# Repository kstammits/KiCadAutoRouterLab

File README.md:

# Karltron Autorouter

> **Status:** Early stage — works on real boards (tube111, DCCF), DRC-validated. Expect rough edges. Use at your own risk.
> Part of the KiCad AutoRouter Lab project.

Pure-Python autorouter for KiCad: drop a `.kicad_pcb` into the web UI or run headless, get routed tracks back. No `pcbnew` scripting, no C++ plugins.

**Workflow: 1 Load → 2 Place (Step / Run + Accept) → 3 Route → 4 DRC + Download.**

| What it does | How you reach it |
|--------------|------------------|
| **Per-pad force placement** — connected pads attract, all pads repel; parts rotate and slide around locked anchors | Place tab → Step / Run / Accept; Regime presets (Scatter start, Placed-board polish, Tidy align); ghosts as keepout walls / attractors |
| **Grid A* routing** — clearance-aware, per-net widths, power-rail overrides, GND pours passable-at-toll with auto-stitching | Route tab → Route (selection, else all unprotected) / Polish (always effort 3) / Select Unrouted / Refine Order; 2-layer / 4-layer mode switch |
| **Power integrity (report only)** — inlet-anchored DC-resistance screening, mated-pair bridges | Route tab → Power integrity + Mated pairs sections |
| **DRC gate** — `kicad-cli pcb drc` runs on writeback; nothing DRC-dirty is stamped silently | Top bar → Run DRC, then Download |
| **Review & share** — motion playback, force vectors, context save/load, copy-link presets | Motion bar, Show proposal / forces toggles, Save/Load ctx, Copy link |

---

## Quick Start (2 minutes)

```bash
git clone https://github.com/kstammits/KiCadAutoRouterLab.git
cd KiCadAutoRouterLab
python -m venv .venv
.venv/bin/pip install -e ".[dev]" --constraint requirements-lock.txt
.venv/bin/python ui/server.py
# Opens http://127.0.0.1:8000
```

1. **Load** — drag `tests/fixtures/tube111.kicad_pcb` onto the page.
2. **Place** — select parts, **Step** (5 iters) or **Run** (to convergence), **Accept**. Alt+click pins a part.
3. **Route** — Route tab → select nets → **Route** (empty selection routes all unprotected); **Polish** re-smooths at full effort without re-searching.
4. **DRC** — tick **DRC**, **Run DRC**, then **Download** the board.

Headless: `scripts/run_autoroute.py board.kicad_pcb -o out.kicad_pcb --step-iterations 5 --max-total-iterations 500`. Same core; the UI adds SVG view, motion playback, sliders.

Test boards: `tests/fixtures/tube111.kicad_pcb` (105 parts, 73 nets) and `tests/fixtures/DCCF.sved.kicad_pcb` (audio, split rails).

---

## Routing Controls

| Control | Typical Range |
|---------|---------------|
| **Track / Power Width** | 0.15–0.25 / 0.4–0.8 mm; per-net override, then netclass, then power flag |
| **Via Cost / Clearance** | 3–10 mm per via; 0.15–0.25 mm spacing |
| **Grid Resolution** | 0.1 mm default (0.15–0.2 for scouting; finer than 0.1 rarely pays) |
| **Smoothing Effort** | 0 = raw search path … 2 = full arcs (default), 3 = high-effort retry (route-time smoothing + auto-polish); the **Polish** button always runs at 3 on its scope (selection, else routed copper) and falls back to a scoped re-route when the board changed since routing |
| **GND Stitching / Strip GND Blockers** | On (2-layer mode) — stitching repairs pour islands; strip evicts only GND copper, never signals |
| **2-layer / 4-layer** | 2-layer collapses to genuine 2-layer on export; 4-layer taps inner planes with stub+vias (`fanout_vias_added`) |

Details live in the manual and glossary (links below), not here.

---

## Keyboard Shortcuts

`A` select unlocked · `Shift+click` multi-select · `Alt+click` pin · wheel zoom · drag pan · `Fit` reset · `Escape` clear.

---

## Performance

Indicative desktop wall-clock (±30%), measured locally — regenerate with `scripts/benchmark_*.py` (`docs/benchmarks/` is untracked; see its README).

| Task | Typical time |
|------|--------------|
| Placement **Step** (5 iters, ~100 parts) | < 1 s |
| Placement **Run** to budget (1000 iters) | ~25–35 s |
| tube111 full signal set (60 nets, 0.1 mm) | ~15 s, 60/60 routed |
| DCCF full signal set (44 nets) | ~45 s |
| GND stitch + pour repair | ~1–3 s |

Rules of thumb: placement costs ~N^1.2–1.5 per iteration — estimate per-iteration cost × iterations. Routing is ~1 s/net on healthy boards.

---

## Learn More

| Doc | What You'll Find |
|-----|------------------|
| [`ui/manual.html`](ui/manual.html) | **User:** Placement manual with live before/after examples (placement only; routing lives in the app Route tab) |
| [`docs/autorouting_glossary.md`](docs/autorouting_glossary.md) | **User:** Pipeline stages, terminology, algorithm guidance |
| [`docs/si_force_laws.md`](docs/si_force_laws.md) | **Dev reference:** Placement force laws and parameter defaults |
| [`docs/physics_primer.qmd`](docs/physics_primer.qmd) | **Dev reference:** Force-law primer with figures and math |
| [`docs/roadmap.md`](docs/roadmap.md) | **Dev:** Open work |
| [`docs/README.md`](docs/README.md) | **Dev:** Upstream references with fetch recipes |

Regenerate the manual/figures with `.venv/bin/python scripts/gen_manual.py`, or everything (figures + manual + primer) with `./scripts/regen_docs.sh [--only-manual | --skip-quarto | --pdf]`.

---

## Requirements

- Python 3.11+, `.venv` with project deps (`pip install -e ".[dev]" --constraint requirements-lock.txt`, ~600 MB with dev extras)
- KiCad 10.x `kicad-cli` for DRC validation (recommended; `pcbnew` module not needed)

---

## License

GPL-3.0-or-later. See [`LICENSE`](LICENSE).

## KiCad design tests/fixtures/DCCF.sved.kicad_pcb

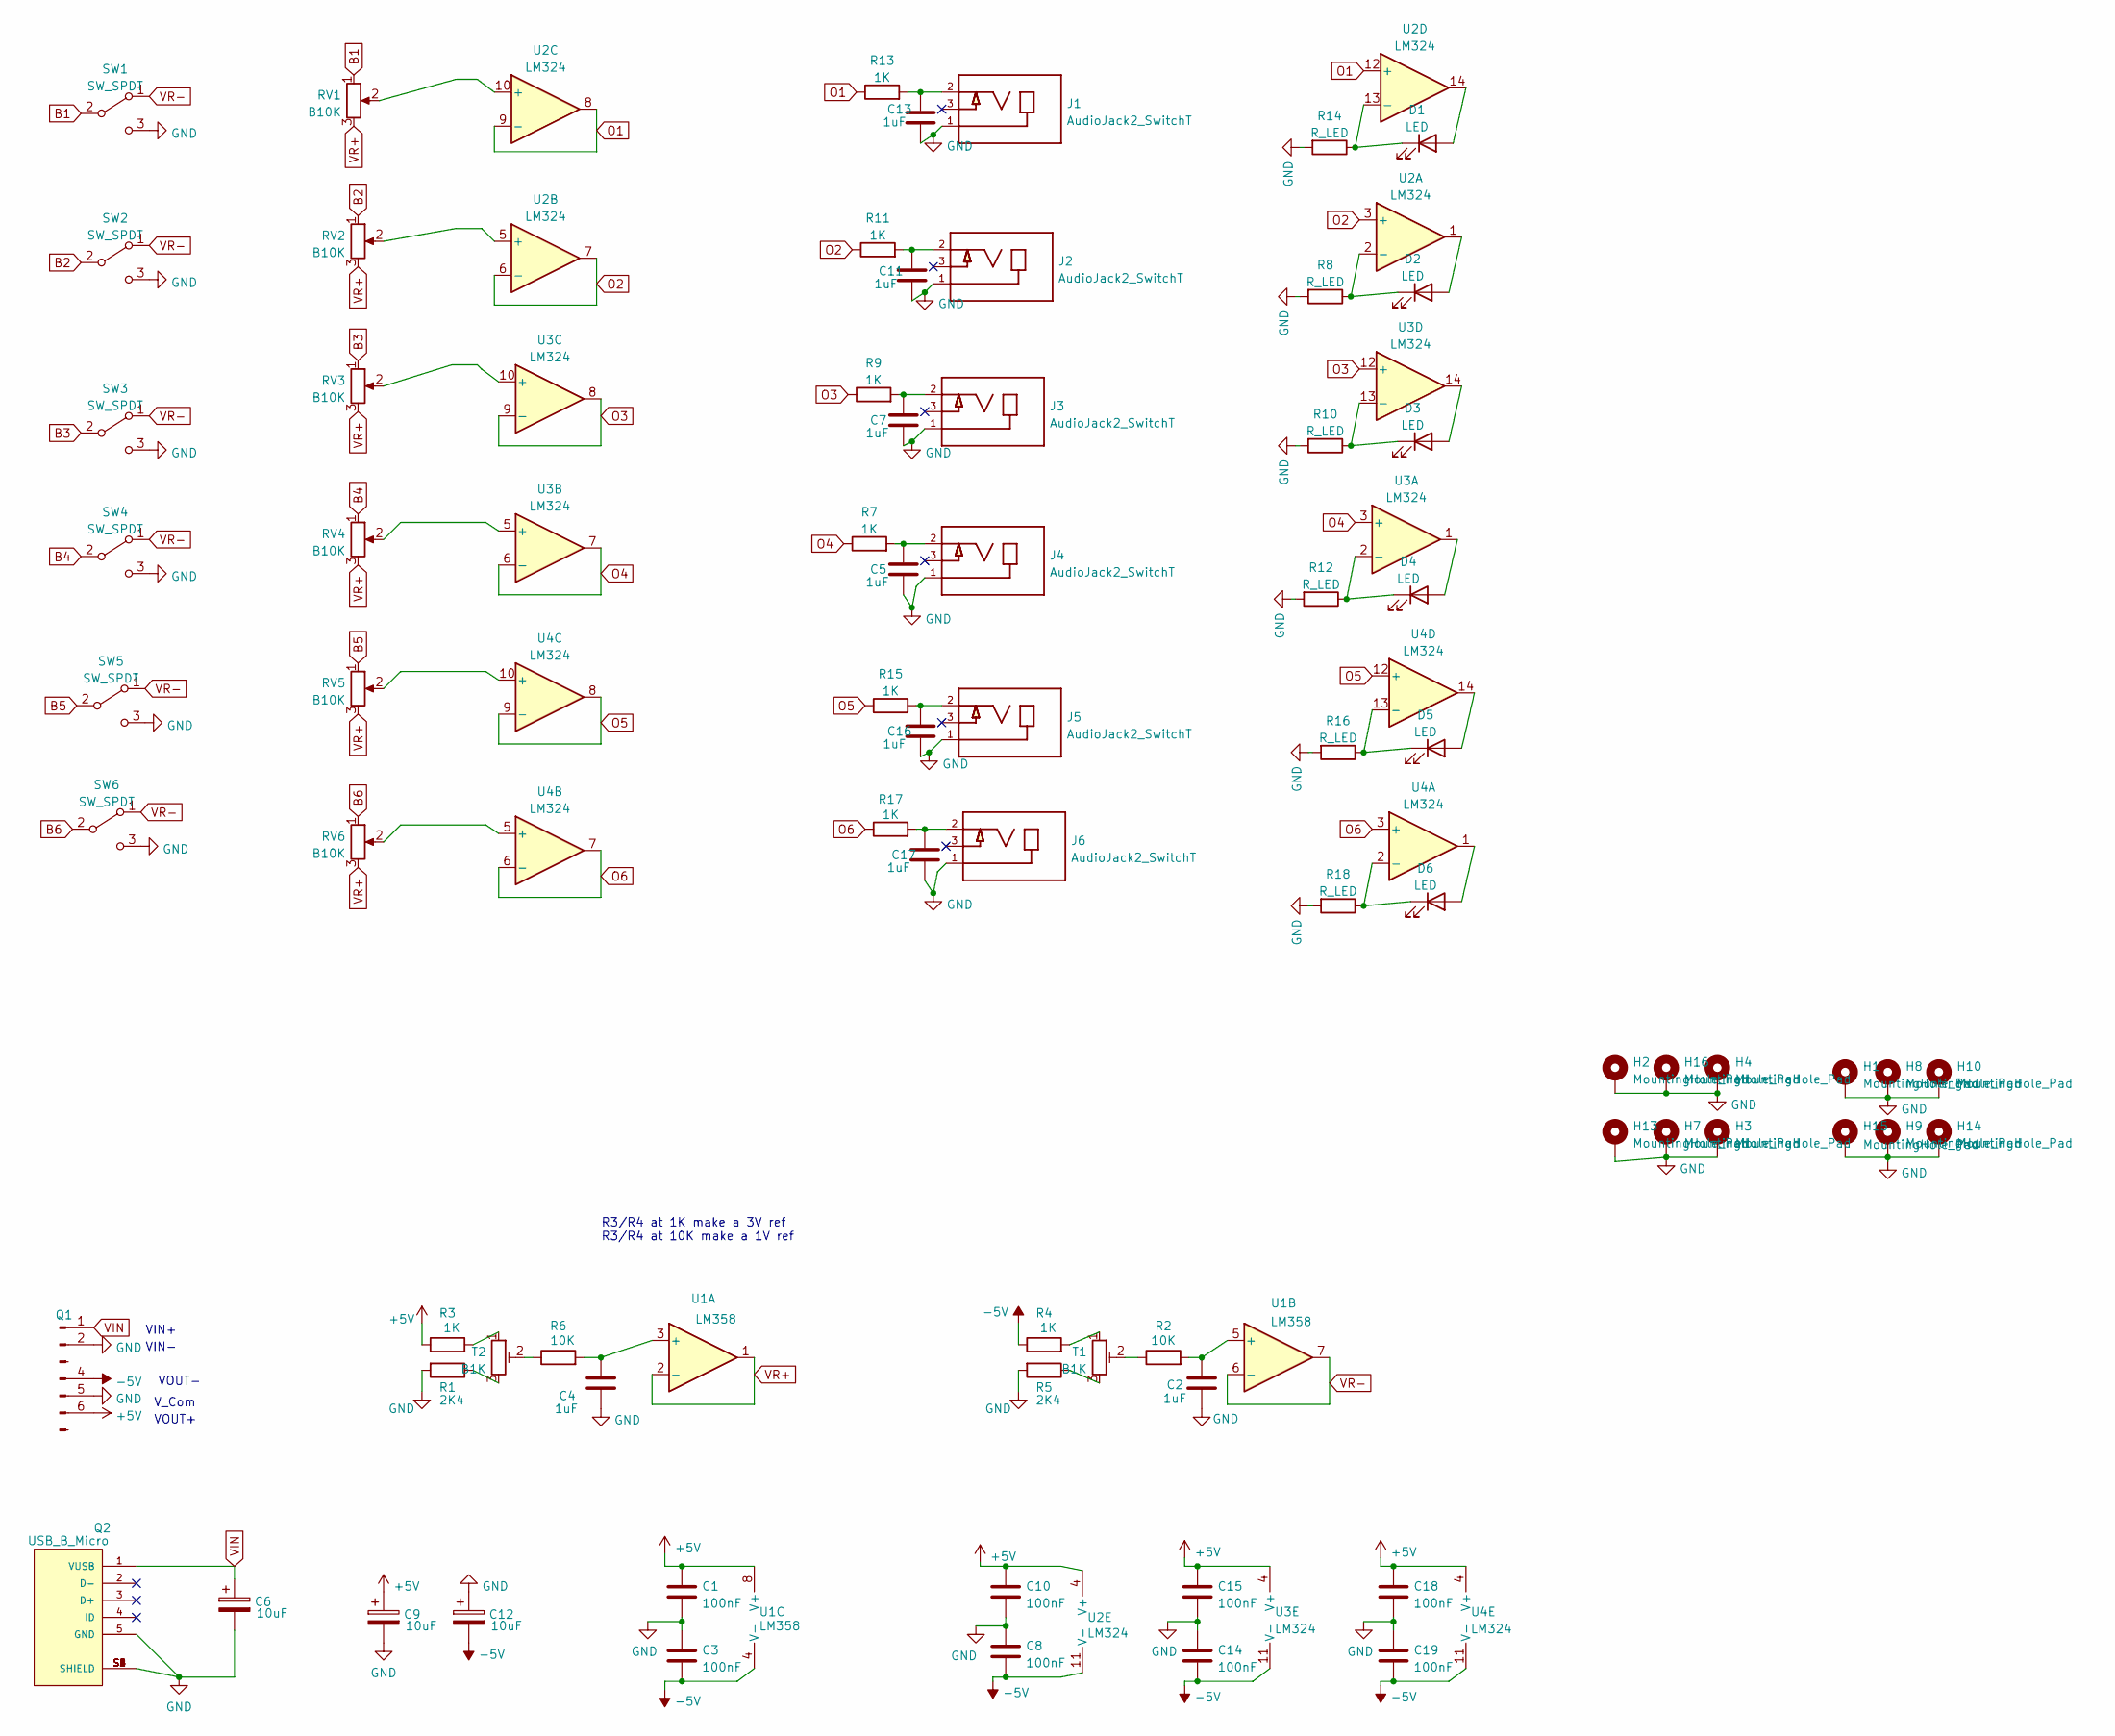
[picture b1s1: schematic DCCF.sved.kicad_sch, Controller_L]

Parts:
C1, C3, C8, C10, C14, C15, C18, C19: 100nF; C_Disc_D5.0mm_W2.5mm_P5.00mm
C2, C4, C5, C7, C11, C13, C16, C17: 1uF; C_Disc_D5.0mm_W2.5mm_P5.00mm
C6, C9, C12: 10uF; CP_Radial_D6.3mm_P2.50mm
D1, D2, D3, D4, D5, D6: LED; LED_D5.0mm
H1, H2, H3, H4, H7, H8, H9, H10, H13, H14, H15, H16: MountingHole_Pad; MountingHole_3.2mm_M3_Pad
J1, J2, J3, J4, J5, J6: AudioJack2_SwitchT; CUI_MJ-3536N; PART_REV B
Q1: Conn_01x07_Male; PinHeader_1x07_P2.54mm_Vertical
Q2: USB_B_Micro; FCI_10118193-0001LF
R1, R5: 2K4; R_Axial_DIN0207_L6.3mm_D2.5mm_P10.16mm_Horizontal
R2, R6: 10K; R_Axial_DIN0207_L6.3mm_D2.5mm_P10.16mm_Horizontal
R3, R4, R7, R9, R11, R13, R15, R17: 1K; R_Axial_DIN0207_L6.3mm_D2.5mm_P10.16mm_Horizontal
R8, R10, R12, R14, R16, R18: R_LED; R_Axial_DIN0207_L6.3mm_D2.5mm_P10.16mm_Horizontal
RV1, RV2: B10K; Potentiometer_Alpha_RD901F-40-00D_Single_Vertical
RV3, RV4, RV5, RV6: B10K; Potentiometer_Bourns_PTA6043_Single_Slide
SW1, SW2, SW3, SW4, SW5, SW6: SW_SPDT; SPDT_Tayda-A5111
T1, T2: B1K; Potentiometer_Bourns_3296W_Vertical
U1: LM358; DIP-8_W7.62mm_Socket
U2, U3, U4: LM324; DIP-14_W7.62mm_Socket

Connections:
+5V: C1.1, C9.1, C10.1, C15.1, C18.1, Q1.6, R3.1, U1.8 (V+), U2.4 (V+), U3.4 (V+), U4.4 (V+)
-5V: C3.2, C8.2, C12.2, C14.2, C19.2, Q1.4, R4.1, U1.4 (V-), U2.11 (V-), U3.11 (V-), U4.11 (V-)
B1: RV1.1, SW1.2 (B)
B2: RV2.1, SW2.2 (B)
B3: RV3.1, SW3.2 (B)
B4: RV4.1, SW4.2 (B)
B5: RV5.1, SW5.2 (B)
B6: RV6.1, SW6.2 (B)
GND: C1.2, C2.2, C3.1, C4.2, C5.2, C6.2, C7.2, C8.1, C9.2, C10.2, C11.2, C12.1, C13.2, C14.1, C15.2, C16.2, C17.2, C18.2, C19.1, H1.1, H2.1, H3.1, H4.1, H7.1, H8.1, H9.1, H10.1, H13.1, H14.1, H15.1, H16.1, J1.1, J2.1, J3.1, J4.1, J5.1, J6.1, Q1.2, Q1.5, Q2.5 (GND), Q2.S1 (SHIELD), Q2.S2 (SHIELD), Q2.S3 (SHIELD), Q2.S4 (SHIELD), Q2.S5 (SHIELD), Q2.S6 (SHIELD), R1.2, R5.2, R8.2, R10.2, R12.2, R14.2, R16.2, R18.2, SW1.3 (C), SW2.3 (C), SW3.3 (C), SW4.3 (C), SW5.3 (C), SW6.3 (C); also elsewhere on the board
unnamed: C2.1, R2.2, U1.5 (+)
unnamed: C4.1, R6.2, U1.3 (+)
unnamed: C5.1, J4.2, R7.2
unnamed: C7.1, J3.2, R9.2
unnamed: C11.1, J2.2, R11.2
unnamed: C13.1, J1.2, R13.2
unnamed: C16.1, J5.2, R15.2
unnamed: C17.1, J6.2, R17.2
unnamed: D1.1 (K), R14.1, U2.13 (-)
unnamed: D1.2 (A), U2.14
unnamed: D2.1 (K), R8.1, U2.2 (-)
unnamed: D2.2 (A), U2.1
unnamed: D3.1 (K), R10.1, U3.13 (-)
unnamed: D3.2 (A), U3.14
unnamed: D4.1 (K), R12.1, U3.2 (-)
unnamed: D4.2 (A), U3.1
unnamed: D5.1 (K), R16.1, U4.13 (-)
unnamed: D5.2 (A), U4.14
unnamed: D6.1 (K), R18.1, U4.2 (-)
unnamed: D6.2 (A), U4.1
unnamed: R1.1, T2.3
unnamed: R2.1, T1.2
unnamed: R3.2, T2.1
unnamed: R4.2, T1.1
unnamed: R5.1, T1.3
unnamed: R6.1, T2.2
unnamed: RV1.2, U2.10 (+)
unnamed: RV2.2, U2.5 (+)
unnamed: RV3.2, U3.10 (+)
unnamed: RV4.2, U3.5 (+)
unnamed: RV5.2, U4.10 (+)
unnamed: RV6.2, U4.5 (+)
O1: R13.1, U2.8, U2.9 (-), U2.12 (+)
O2: R11.1, U2.3 (+), U2.6 (-), U2.7
O3: R9.1, U3.8, U3.9 (-), U3.12 (+)
O4: R7.1, U3.3 (+), U3.6 (-), U3.7
O5: R15.1, U4.8, U4.9 (-), U4.12 (+)
O6: R17.1, U4.3 (+), U4.6 (-), U4.7
VIN: C6.1, Q1.1, Q2.1 (VUSB)
VR+: RV1.3, RV2.3, RV3.3, RV4.3, RV5.3, RV6.3, U1.1, U1.2 (-)
VR-: SW1.1 (A), SW2.1 (A), SW3.1 (A), SW4.1 (A), SW5.1 (A), SW6.1 (A), U1.6 (-), U1.7

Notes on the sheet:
VIN-
R3/R4 at 1K make a 3V ref R3/R4 at 10K make a 1V ref
VOUT+
V_Com
VOUT-
VIN+

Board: 2 copper layers, 87 parts (0 on the bottom side), 50 nets, no tracks yet.

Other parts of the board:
H5, H6, H6#2, H6#3, H6#4, H6#5: MountingHole_Pad; MountingHole_3.2mm_M3_Pad

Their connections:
GND: H5.1, H6.1, H6#2.1, H6#3.1, H6#4.1, H6#5.1; also elsewhere on the board

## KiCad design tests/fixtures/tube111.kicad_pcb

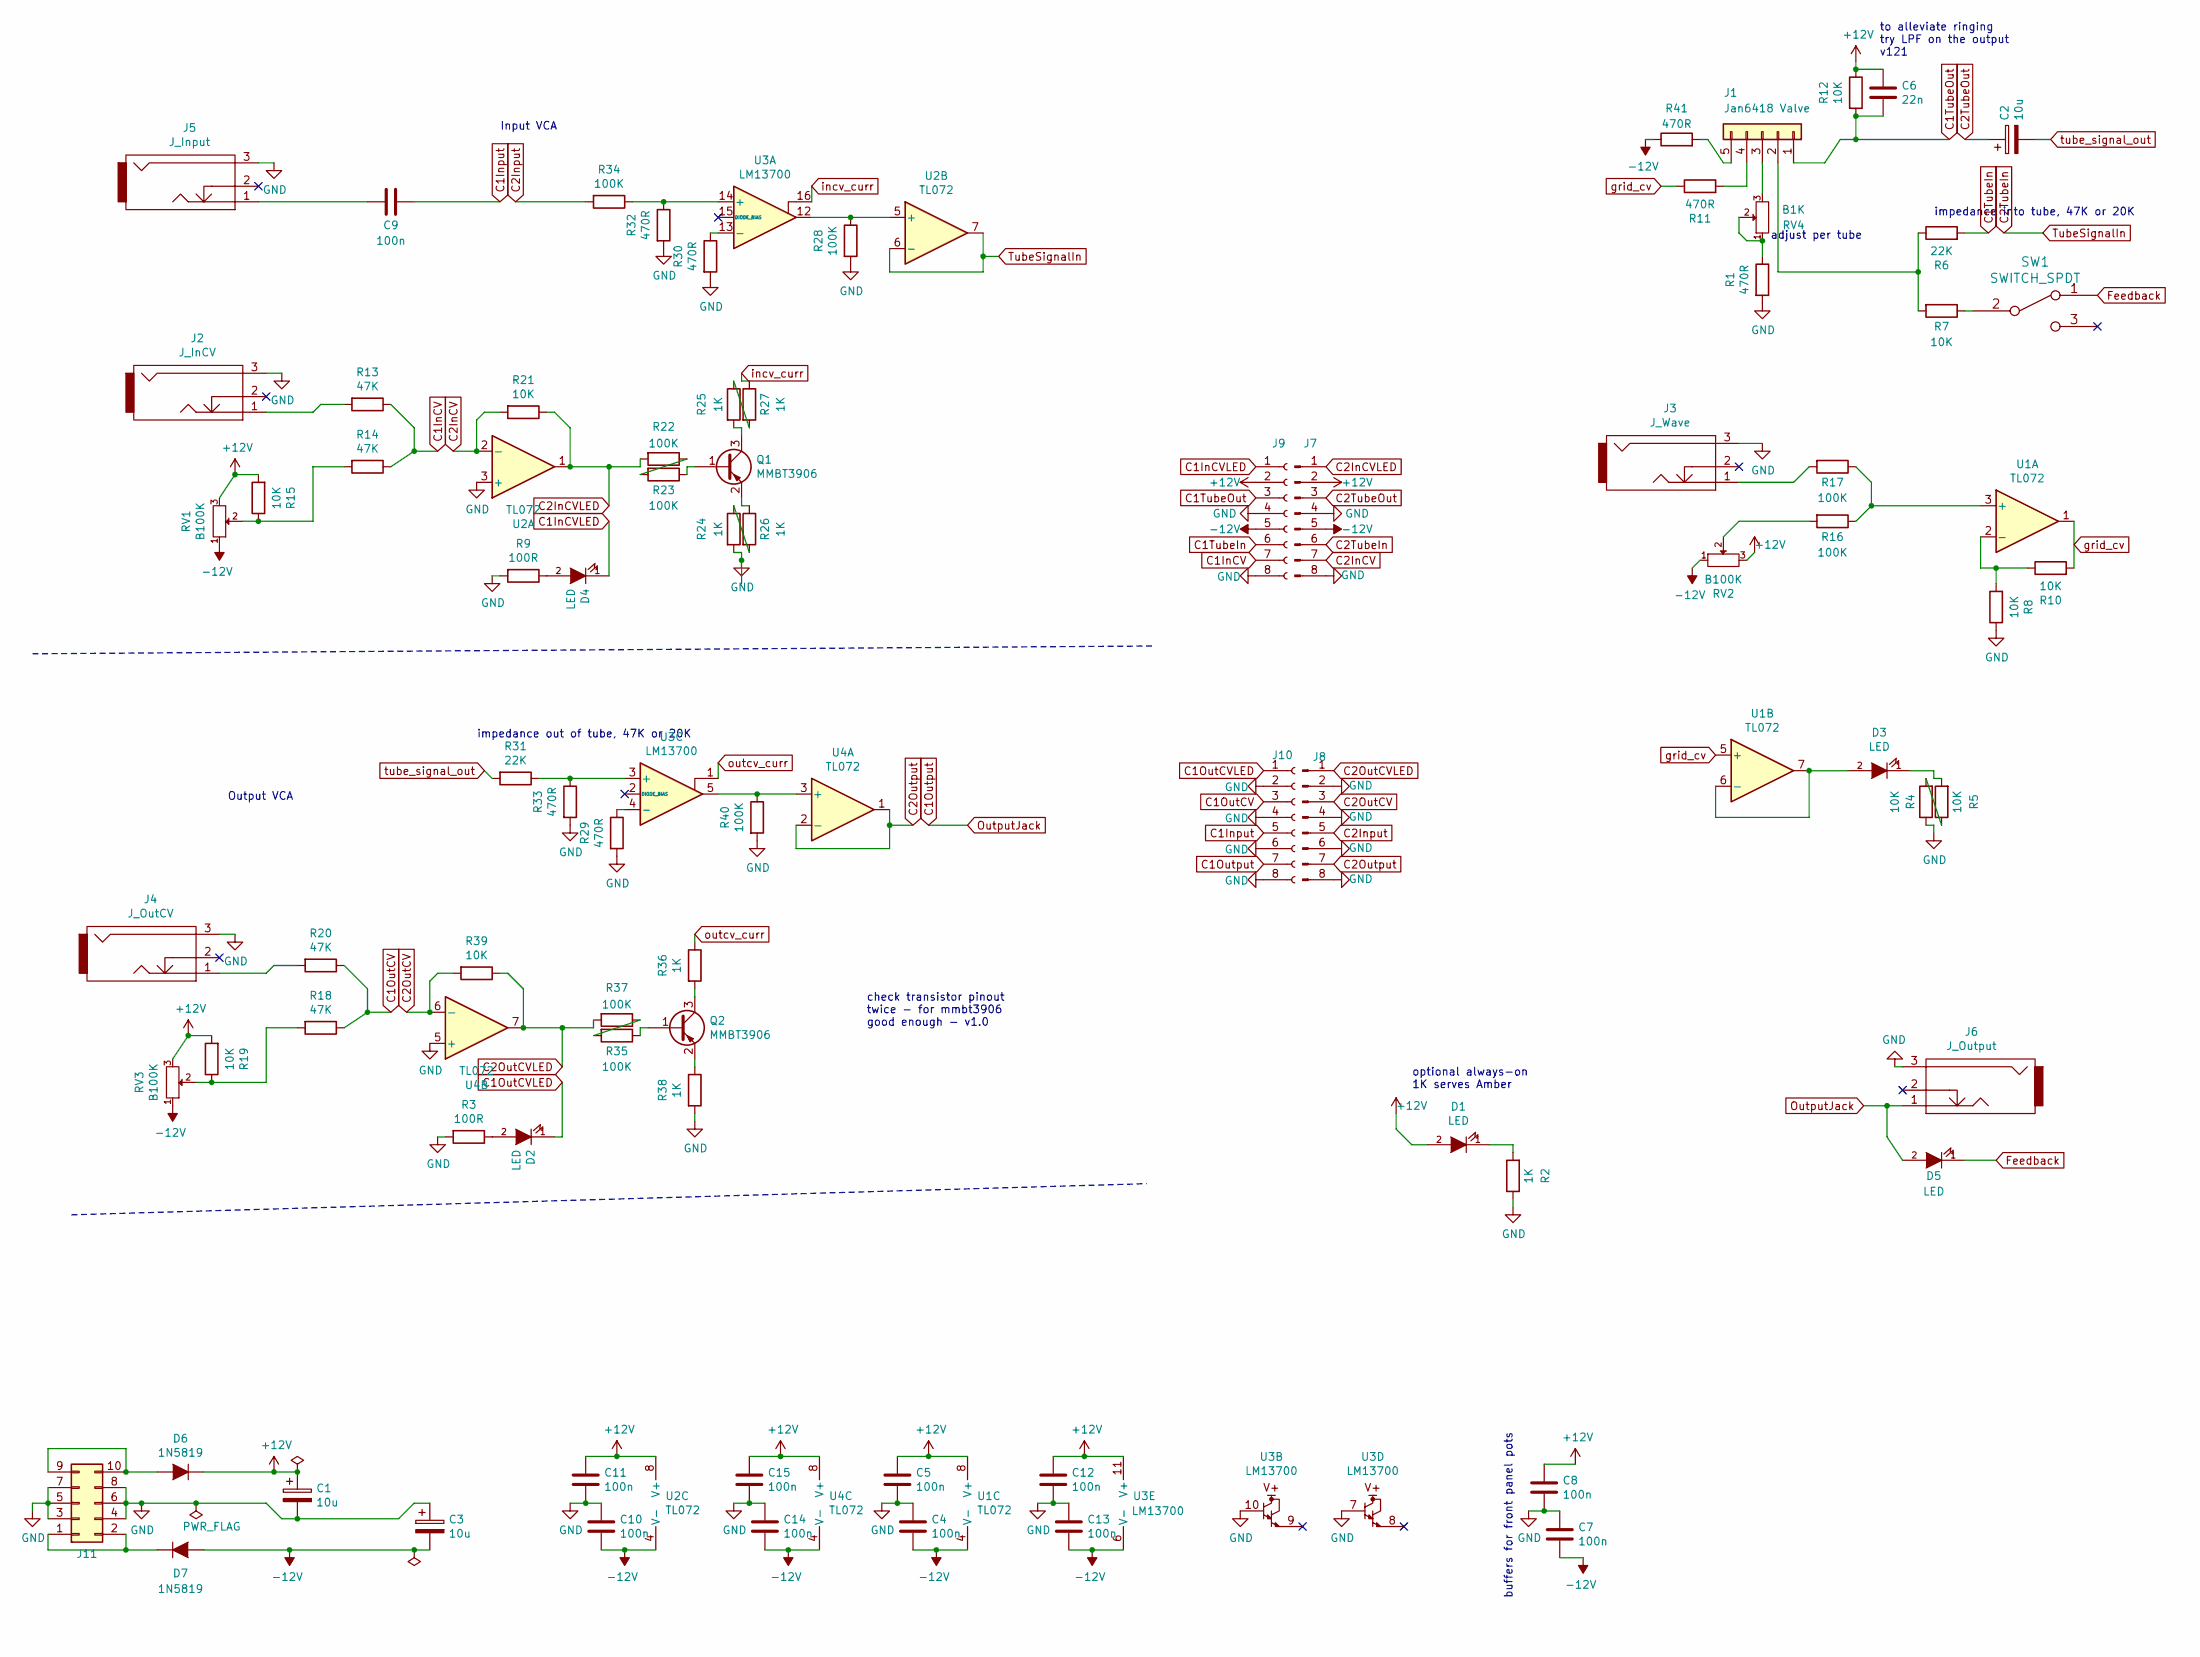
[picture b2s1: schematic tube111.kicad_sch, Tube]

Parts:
C1, C2, C3: 10u; CP_Radial_D5.0mm_P2.50mm
C4, C5, C7, C8, C9, C10, C11, C12, C13, C14, C15: 100n; C_0805_2012Metric_Pad1.18x1.45mm_HandSolder
C6: 22n; C_0805_2012Metric_Pad1.18x1.45mm_HandSolder
D1, D2, D3, D4, D5: LED; LED_D5.0mm
D6, D7: 1N5819; D_DO-41_SOD81_P10.16mm_Horizontal
J1: Jan6418 Valve; PinHeader_1x05_P2.54mm_Vertical
J2: J_InCV; Thonkiconn
J3: J_Wave; Thonkiconn
J4: J_OutCV; Thonkiconn
J5: J_Input; Thonkiconn
J6: J_Output; Thonkiconn
J7, J8: Conn_01x08_Male; PinHeader_1x08_P2.54mm_Vertical
J9, J10: Conn_01x08_Female; PinHeader_1x08_P2.54mm_Vertical
J11: Conn_02x05_Odd_Even; PinHeader_2x05_P2.54mm_Vertical
Q1, Q2: MMBT3906; SOT-23
R1, R11, R29, R30, R32, R33, R41: 470R; R_0805_2012Metric_Pad1.20x1.40mm_HandSolder
R2, R24, R25, R26, R27, R36, R38: 1K; R_0805_2012Metric_Pad1.20x1.40mm_HandSolder
R3, R9: 100R; R_0805_2012Metric_Pad1.20x1.40mm_HandSolder
R4, R5, R7, R8, R10, R12, R15, R19, R21, R39: 10K; R_0805_2012Metric_Pad1.20x1.40mm_HandSolder
R6, R31: 22K; R_0805_2012Metric_Pad1.20x1.40mm_HandSolder
R13, R14, R18, R20: 47K; R_0805_2012Metric_Pad1.20x1.40mm_HandSolder
R16, R17, R22, R23, R28, R34, R35, R37, R40: 100K; R_0805_2012Metric_Pad1.20x1.40mm_HandSolder
RV1, RV2, RV3: B100K; Potentiometer_Alpha_RD901F-40-00D_Single_Vertical
RV4: B1K; Potentiometer_Bourns_3296W_Vertical
SW1: SWITCH_SPDT; SPDT_Sip3
U1, U2, U4: TL072; SOIC-8_3.9x4.9mm_P1.27mm
U3: LM13700; SOIC-16_3.9x9.9mm_P1.27mm

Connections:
+12V: C1.1, C5.1, C6.1, C8.1, C11.1, C12.1, C15.1, D1.2 (A), D6.1 (K), J7.2, J9.2, R12.1, R15.2, R19.2, RV1.3, RV2.3, RV3.3, U1.8 (V+), U2.8 (V+), U3.11 (V+), U4.8 (V+)
-12V: C3.2, C4.2, C7.2, C10.2, C13.2, C14.2, D7.2 (A), J7.5, J9.5, R41.1, RV1.1, RV2.1, RV3.1, U1.4 (V-), U2.4 (V-), U3.6 (V-), U4.4 (V-)
C1InCV: J9.7, R13.1, R14.1
C1InCVLED: D4.1 (K), J9.1
C1Input: C9.1, J10.5
C1OutCV: J10.3, R18.1, R20.1
C1OutCVLED: D2.1 (K), J10.1
C1Output: D5.2 (A), J6.1, J10.7
C1TubeIn: J9.6, R6.2
C1TubeOut: C6.2, J1.1, J9.3, R12.2
C2InCV: J7.7, R21.2, U2.2 (-)
C2InCVLED: J7.1, R21.1, R22.2, U2.1
C2Input: J8.5, R34.2
C2OutCV: J8.3, R39.2, U4.6 (-)
C2OutCVLED: J8.1, R37.2, R39.1, U4.7
C2Output: J8.7, U4.1, U4.2 (-)
C2TubeIn: J7.6, U2.6 (-), U2.7
C2TubeOut: C2.1, J7.3
Feedback: D5.1 (K), SW1.1
GND: C1.2, C3.1, C4.1, C5.2, C7.1, C8.2, C10.1, C11.2, C12.2, C13.1, C14.1, C15.2, J2.3, J3.3, J4.3, J5.3, J6.3, J7.4, J7.8, J8.2, J8.4, J8.6, J8.8, J9.4, J9.8, J10.2, J10.4, J10.6, J10.8, J11.3, J11.4, J11.5, J11.6, J11.7, J11.8, R1.2, R2.1, R3.2, R4.1, R8.1, R9.2, R24.2, R28.2, R29.2, R30.2, R32.2, R33.2, R38.2, R40.2, U2.3 (+), U3.7, U3.10, U4.5 (+)
unnamed: C9.2, J5.1
unnamed: D1.1 (K), R2.2
unnamed: D2.2 (A), R3.1
unnamed: D3.1 (K), R5.2
unnamed: D3.2 (A), U1.6 (-), U1.7
unnamed: D4.2 (A), R9.1
unnamed: D6.2 (A), J11.9, J11.10
unnamed: D7.1 (K), J11.1, J11.2
unnamed: J1.2, R6.1, R7.2
unnamed: J1.3, RV4.3
unnamed: J1.4, R11.2
unnamed: J1.5, R41.2
unnamed: J2.1, R13.2
unnamed: J3.1, R17.2
unnamed: J4.1, R20.2
unnamed: Q1.1 (B), R23.1
unnamed: Q1.2 (E), R26.1
unnamed: Q1.3 (C), R25.2
unnamed: Q2.1 (B), R35.1
unnamed: Q2.2 (E), R38.1
unnamed: Q2.3 (C), R36.2
unnamed: R1.1, RV4.1, RV4.2
unnamed: R4.2, R5.1
unnamed: R7.1, SW1.2
unnamed: R8.2, R10.1, U1.2 (-)
unnamed: R14.2, R15.1, RV1.2
unnamed: R16.1, R17.1, U1.3 (+)
unnamed: R16.2, RV2.2
unnamed: R18.2, R19.1, RV3.2
unnamed: R22.1, R23.2
unnamed: R24.1, R26.2
unnamed: R25.1, R27.2
unnamed: R28.1, U2.5 (+), U3.12
unnamed: R29.1, U3.4 (-)
unnamed: R30.1, U3.13 (-)
unnamed: R31.1, R33.1, U3.3 (+)
unnamed: R32.1, R34.1, U3.14 (+)
unnamed: R35.2, R37.1
unnamed: R40.1, U3.5, U4.3 (+)
grid_cv: R10.2, R11.1, U1.1, U1.5 (+)
incv_curr: R27.1, U3.16
outcv_curr: R36.1, U3.1
tube_signal_out: C2.2, R31.2

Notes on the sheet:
impedance into tube, 47K or 20K
adjust per tube
buffers for front panel pots
check transistor pinout twice - for mmbt3906 good enough - v1.0
impedance out of tube, 47K or 20K
to alleviate ringing try LPF on the output v121
Input VCA
optional always-on 1K serves Amber
Output VCA

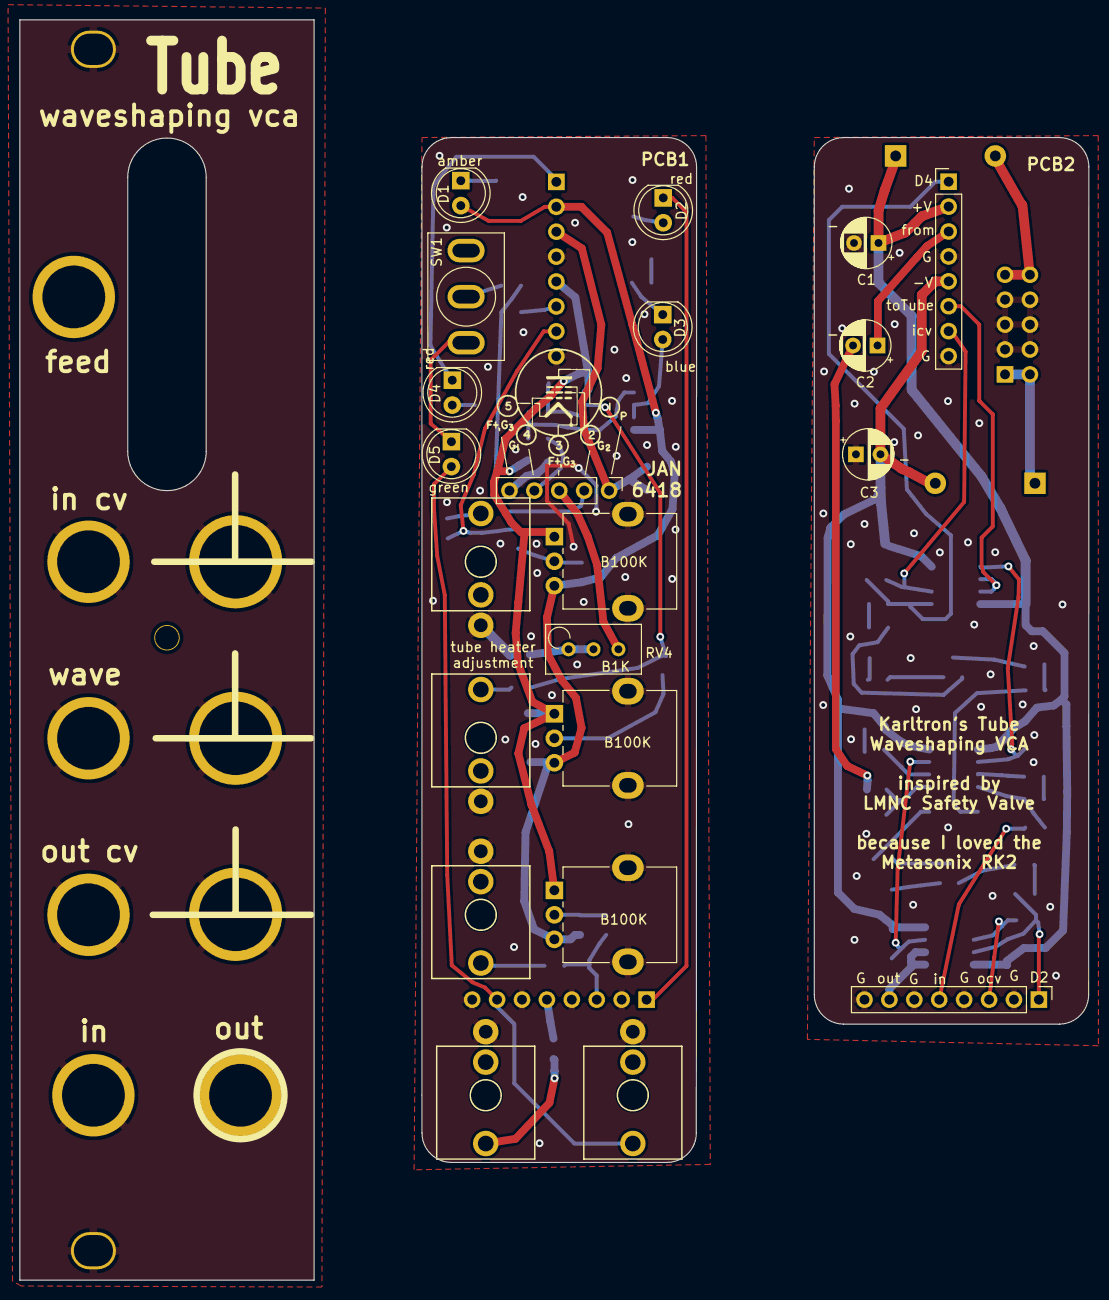
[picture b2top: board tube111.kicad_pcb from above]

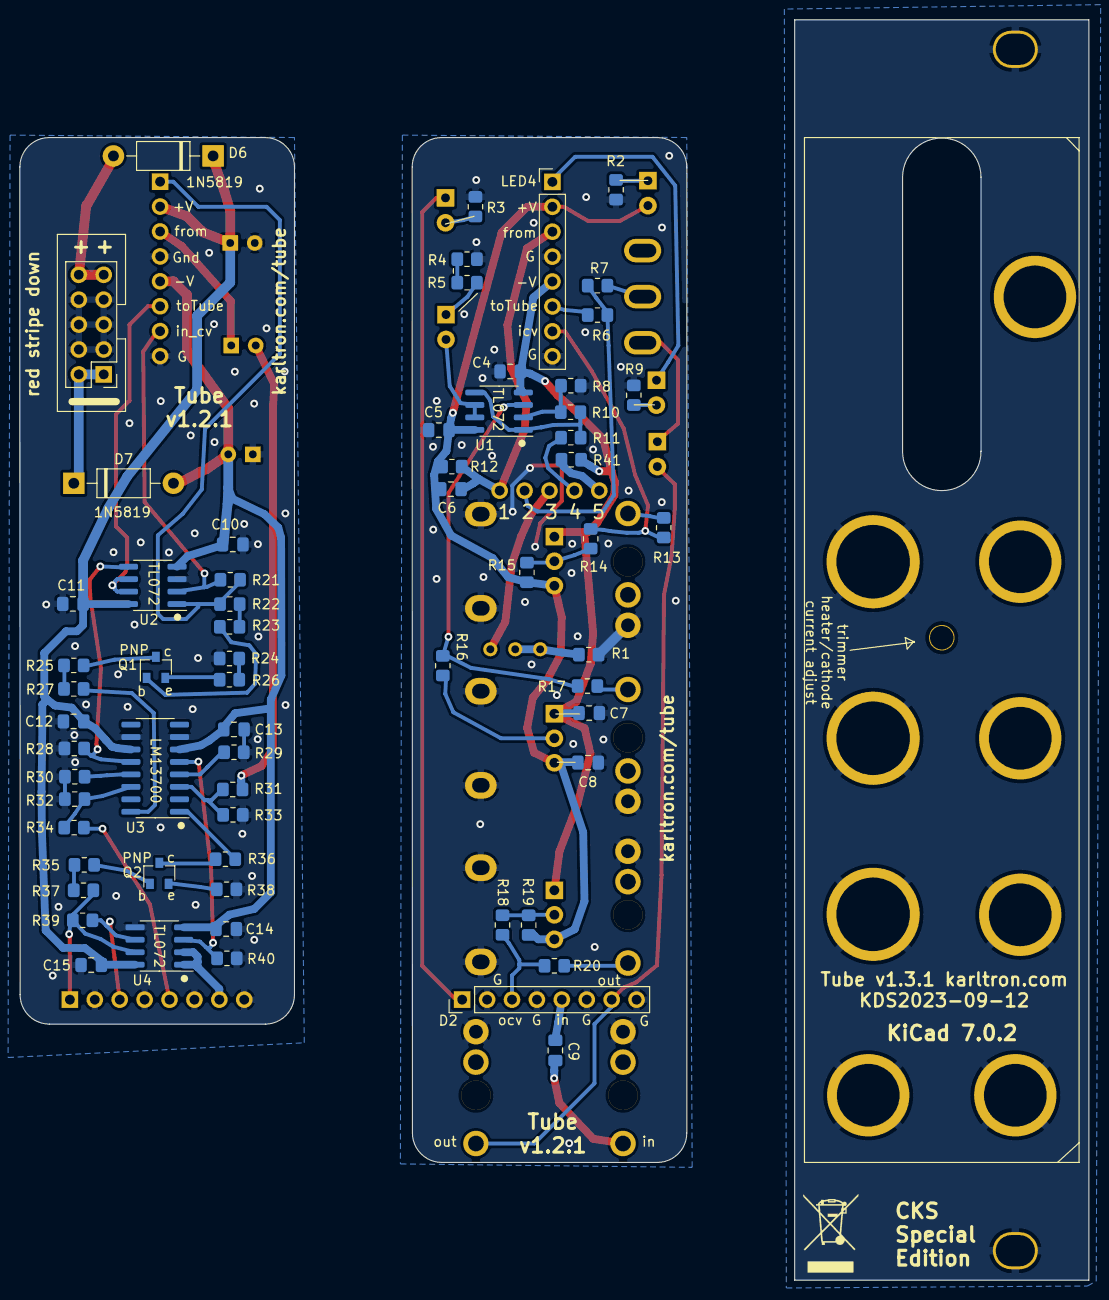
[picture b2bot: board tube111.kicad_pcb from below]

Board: 2 copper layers, 109.0 x 128.5 mm, 85 parts (64 on the bottom side), 63 nets.

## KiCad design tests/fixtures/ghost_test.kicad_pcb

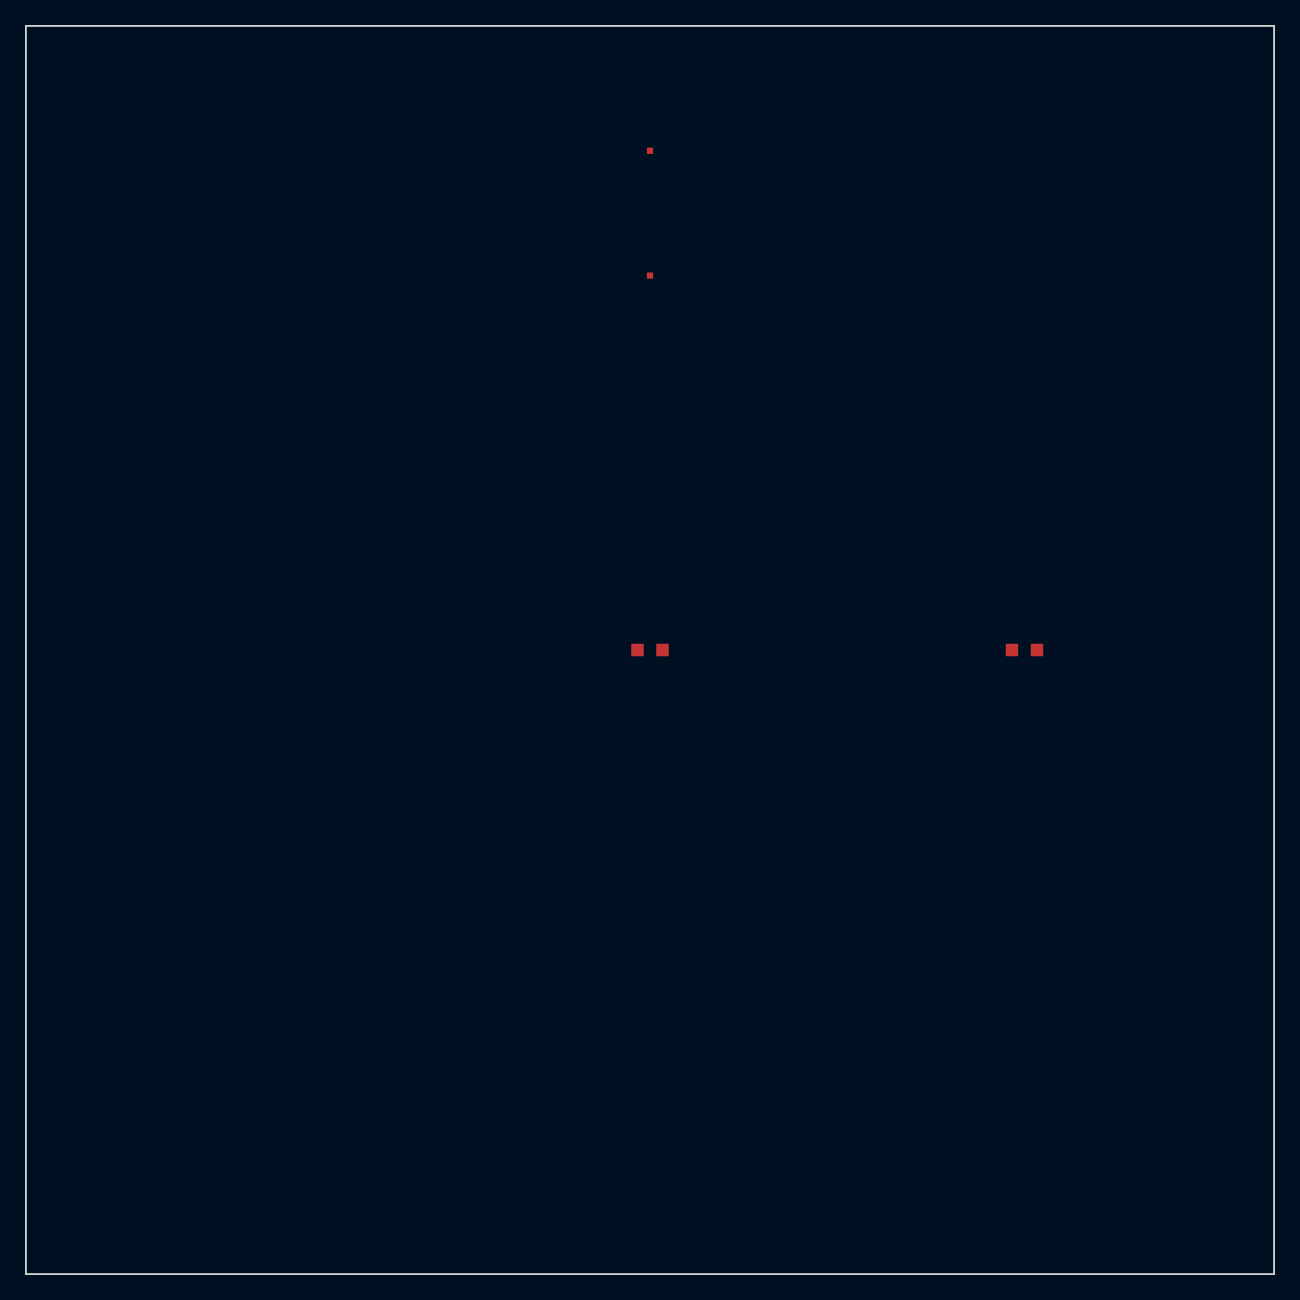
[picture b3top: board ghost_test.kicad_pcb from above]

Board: 1 copper layer, 100.0 x 100.0 mm, 4 parts (0 on the bottom side), 2 nets, no tracks yet.

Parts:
GHOST_FERRULE: Ferrule
GHOST_RAIL_TOP: Rail_10mm
R2: 10k; R_0805
U1: IC_TEST; R_0805

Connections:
NET1: R2.1, U1.1
NET2: R2.2, U1.2
